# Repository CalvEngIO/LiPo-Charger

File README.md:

# LiPo-Charger
Calvary Engineering's design for a lithium polymer (LiPo) battery charger using the MCP73831T

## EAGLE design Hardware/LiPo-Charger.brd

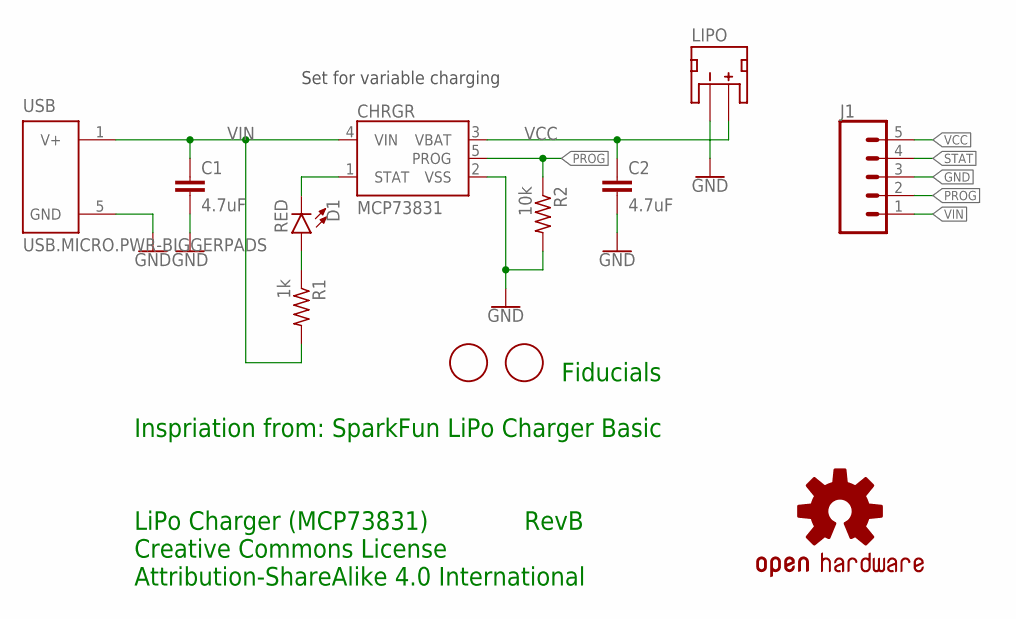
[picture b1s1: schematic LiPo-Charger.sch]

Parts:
C1, C2: 4.7uF; C0603
CHRGR: MCP73831; SOT23-5
D1: RED; LED-0603
J1: CONN_05; 1X05
JP3, JP4: FIDUCIAL; FIDUCIAL_1MM
LIPO: JST_2MM_MALE; JST-2-SMD
LOGO1: OSHW-LOGOS; OSHW-LOGO-S
R1: 1k; R0402
R2: 10k; R0402
U$1: CALVENGIO_HANDLEHANDLE.08; CALVENGIO_HANDLE.08
USB: USB.MICRO.PWR-BIGGERPADS; USB-MICRO-01.BIGGERPADS.PWR

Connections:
GND: C1.2, C2.2, CHRGR.2 (VSS), J1.3, LIPO.1 (-), R2.2, USB.5 (GND)
unnamed: D1.A, R1.1
PROG: CHRGR.5 (PROG), J1.2, R2.1
STAT: CHRGR.1 (STAT), D1.C, J1.4
VCC: C2.1, CHRGR.3 (VBAT), J1.5, LIPO.2 (+)
VIN: C1.1, CHRGR.4 (VIN), J1.1, R1.2, USB.1 (V+)

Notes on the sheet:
Set for variable charging
Inspriation from: SparkFun LiPo Charger Basic
LiPo Charger (MCP73831)
Creative Commons License Attribution-ShareAlike 4.0 International
RevB
Fiducials

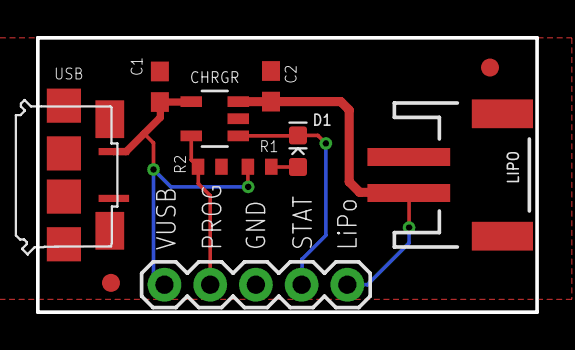
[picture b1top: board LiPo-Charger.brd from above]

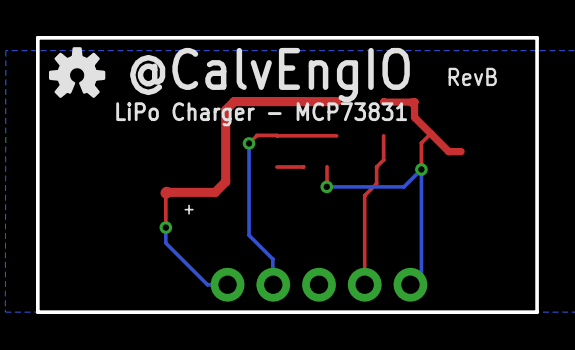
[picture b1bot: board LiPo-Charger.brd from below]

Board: 2 copper layers, 27.7 x 15.2 mm, 13 parts (2 on the bottom side), 6 nets.
